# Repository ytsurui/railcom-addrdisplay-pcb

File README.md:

# Railcom (BiDi) Display Unit PCB Data

NMRA DCCの双方向通信規格 (BiDi, Railcom) に準拠した通信信号を受信し、DCC車両のアドレスを表示する機器の基板設計データです。 \
マイコンが取り外せ、基板上に通信信号を横取りできる端子が設けてあるため、Railcom対応機器の開発ベースとしても利用できます。

本リポジトリには、回路図、基板設計データを含みます。

### 主要スペック

  * Railcom Display Unitを介して接続した線路上で動作している、Railcom対応デコーダの車両アドレスを7セグLEDに表示
  * Railcom Channel1 app:adr_low / app_adr_highの受信に対応 \
    (それ以外のRailcomパケットは無視します)

### 動作確認した環境
#### コマンドステーション
  * Roco Z21

#### デコーダー
  * Lenz SILVER+ Mini

### 閲覧・編集に必要なCAD (開発環境)
  * KiCad Version (5.1.9)-1 (またはそれ以降)

### 対応するファームウェア
  * [Railcom Train Address Display Unit Firmware for ATtiny2313](https://github.com/ytsurui/railcom-addrdisplay-firmware)

### 各種ドキュメント
  * [パーツリスト](docs/partslist.md)

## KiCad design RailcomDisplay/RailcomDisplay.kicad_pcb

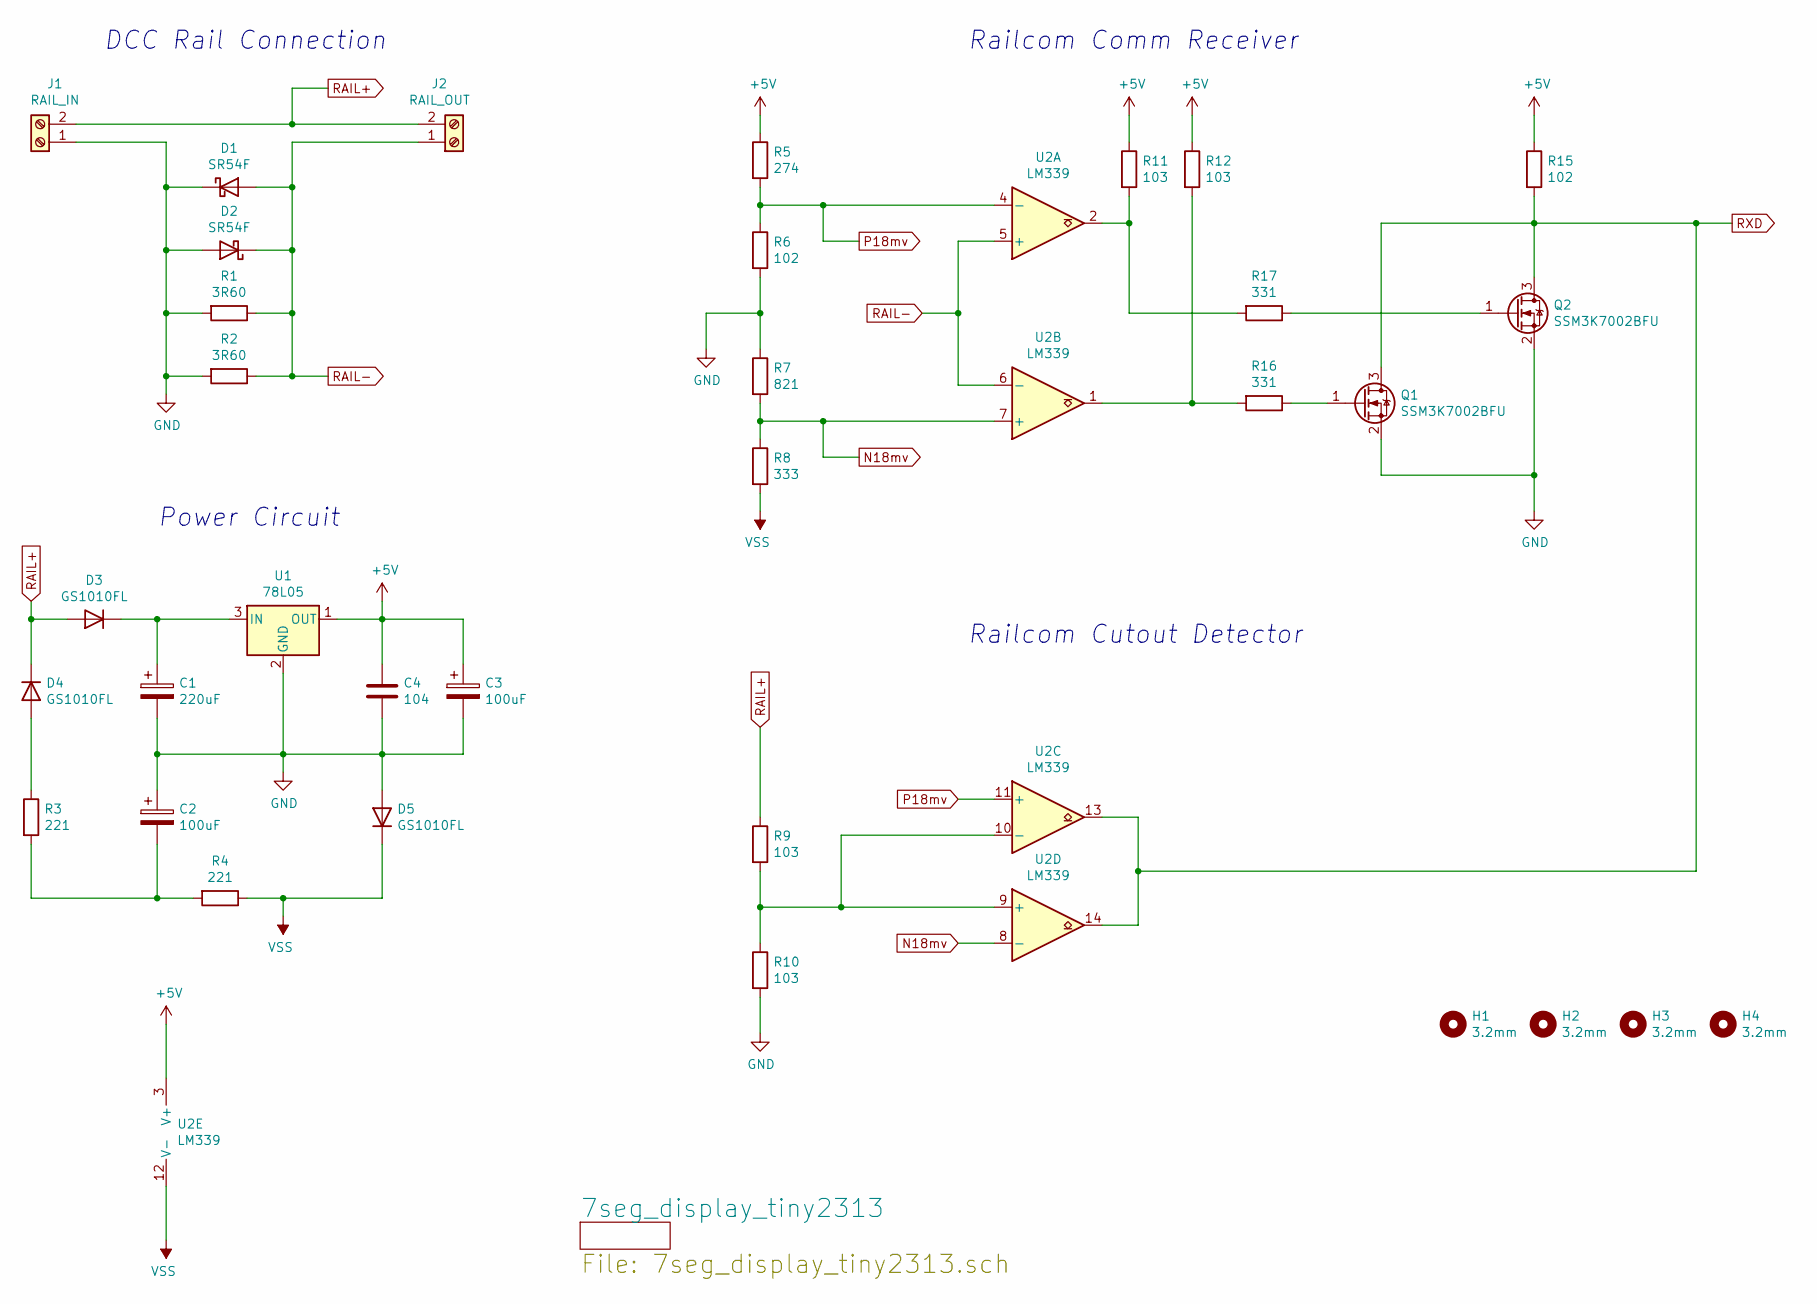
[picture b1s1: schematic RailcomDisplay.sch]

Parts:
C1: 220uF; CAP_TH_6.3x11
C2, C3: 100uF; CAP_TH_5x11
C4: 104; C_1005
D1, D2: SR54F; SMBF
D3, D4, D5: GS1010FL; SOD-123FL
H1, H2, H3, H4: 3.2mm; HOLE_3.2mm
J1: RAIL_IN; TB111-2
J2: RAIL_OUT; TB111-2
Q1, Q2: SSM3K7002BFU; SC-70
R1, R2: 3R60; R_3225
R3, R4: 221; R_1608
R5: 274; R_1608
R6, R15: 102; R_1608
R7: 821; R_1608
R8: 333; R_1608
R9, R10, R11, R12: 103; R_1608
R16, R17: 331; R_1608
U1: 78L05; SOT-89-3
U2: LM339; SOIC-14

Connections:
+5V: C3.1, C4.1, R5.1, R11.1, R12.1, R15.1, U1.1 (OUT), U2.3 (V+); also elsewhere on the board
GND: C1.2, C2.1, C3.2, C4.2, D1.1 (K), D2.2 (A), D5.2 (A), J1.1, Q1.2 (S), Q2.2 (S), R1.2, R2.2, R6.2, R7.1, R10.2, U1.2 (GND); also elsewhere on the board
N18mv: R7.2, R8.1, U2.7 (+), U2.8 (-)
unnamed: C1.1, D3.1 (K), U1.3 (IN)
unnamed: C2.2, R3.2, R4.2
unnamed: D4.2 (A), R3.1
unnamed: Q1.1 (G), R16.1
unnamed: Q2.1 (G), R17.1
unnamed: R9.2, R10.1, U2.9 (+), U2.10 (-)
unnamed: R11.2, R17.2, U2.2
unnamed: R12.2, R16.2, U2.1
P18mv: R5.2, R6.1, U2.4 (-), U2.11 (+)
RAIL+: D3.2 (A), D4.1 (K), J1.2, J2.2, R9.1
RAIL-: D1.2 (A), D2.1 (K), J2.1, R1.1, R2.1, U2.5 (+), U2.6 (-)
RXD: Q1.3 (D), Q2.3 (D), R15.2, U2.13, U2.14; also elsewhere on the board
VSS: D5.1 (K), R4.1, R8.2, U2.12 (V-)

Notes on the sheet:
Railcom Cutout Detector
Power Circuit
DCC Rail Connection
Railcom Comm Receiver

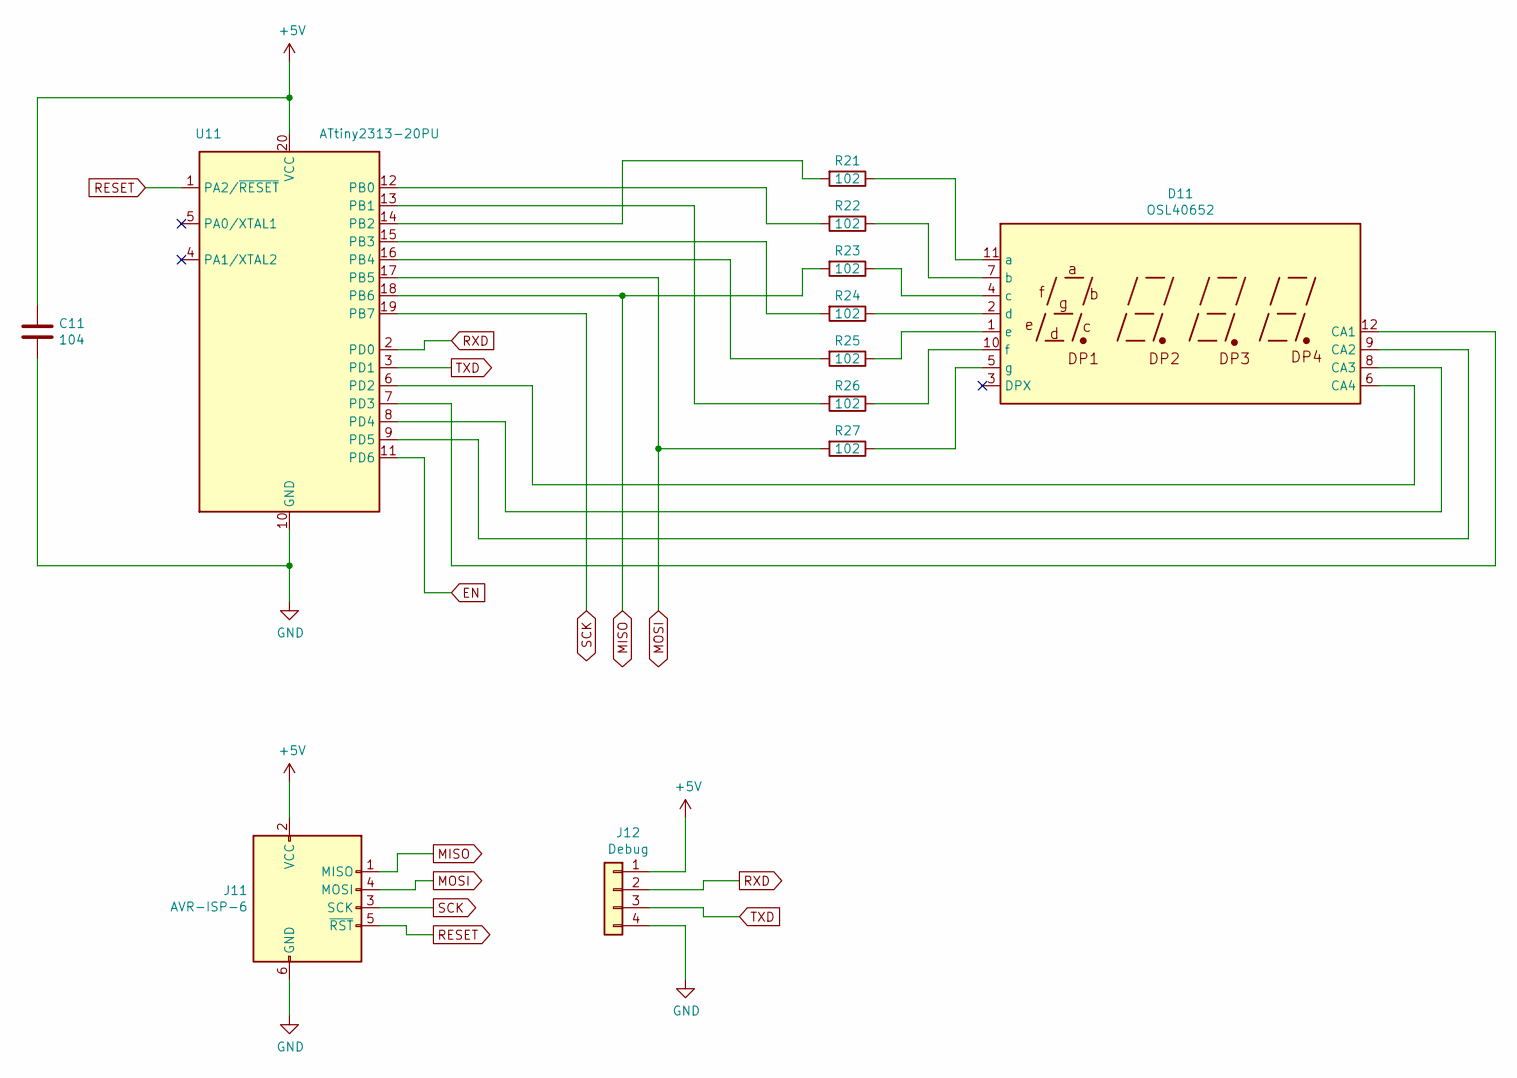
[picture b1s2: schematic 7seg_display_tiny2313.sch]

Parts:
C11: 104; C_1005
D11: OSL40652; OSL40562
J11: AVR-ISP-6; pin_array_3x2_Block
J12: Debug; pin_array_1x4
R21, R22, R23, R24, R25, R26, R27: 102; R_1608
U11: ATtiny2313-20PU; PDIP20

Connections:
+5V: C11.1, J11.2 (VCC), J12.1, U11.20 (VCC); also elsewhere on the board
EN: U11.11 (PD6)
GND: C11.2, J11.6 (GND), J12.4, U11.10 (GND); also elsewhere on the board
MISO: J11.1 (MISO), R23.2, U11.18 (PB6)
MOSI: J11.4 (MOSI), R27.2, U11.17 (PB5)
unnamed: D11.1 (e), R25.1
unnamed: D11.2 (d), R24.1
unnamed: D11.4 (c), R23.1
unnamed: D11.5 (g), R27.1
unnamed: D11.6 (CA4), U11.6 (PD2)
unnamed: D11.7 (b), R22.1
unnamed: D11.8 (CA3), U11.8 (PD4)
unnamed: D11.9 (CA2), U11.9 (PD5)
unnamed: D11.10 (f), R26.1
unnamed: D11.11 (a), R21.1
unnamed: D11.12 (CA1), U11.7 (PD3)
unnamed: R21.2, U11.14 (PB2)
unnamed: R22.2, U11.12 (PB0)
unnamed: R24.2, U11.15 (PB3)
unnamed: R25.2, U11.16 (PB4)
unnamed: R26.2, U11.13 (PB1)
RESET: J11.5 (~RST), U11.1 (PA2/~RESET)
RXD: J12.2, U11.2 (PD0); also elsewhere on the board
SCK: J11.3 (SCK), U11.19 (PB7)
TXD: J12.3, U11.3 (PD1)

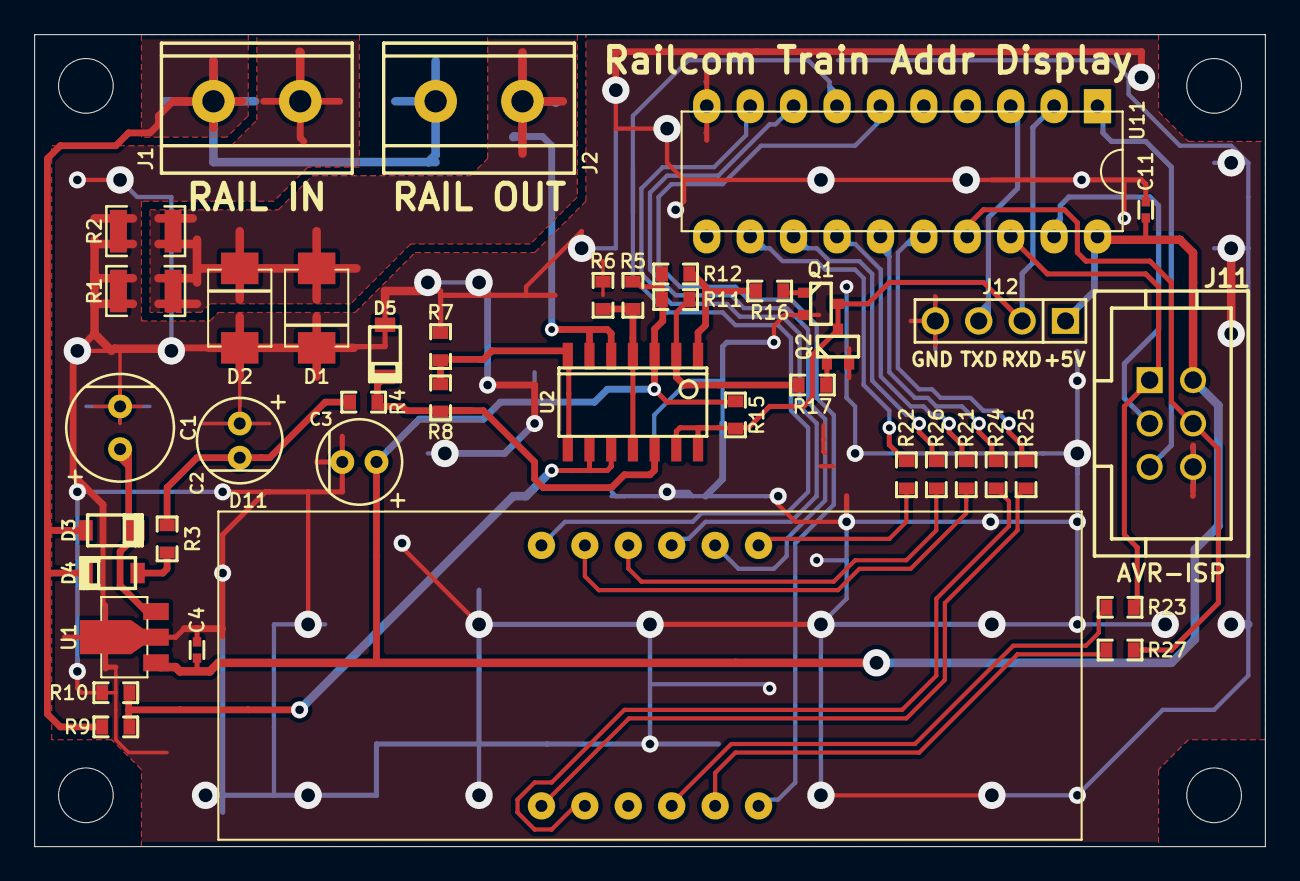
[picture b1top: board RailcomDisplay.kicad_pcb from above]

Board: 2 copper layers, 72.0 x 47.5 mm, 46 parts (0 on the bottom side), 37 nets.
